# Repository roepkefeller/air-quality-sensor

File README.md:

# Air Quality Sensor

A DIY open-source air quality monitor built around an [ESP32-C3-WROOM-02](https://documentation.espressif.com/esp32-c3-wroom-02_datasheet_en.pdf), featuring a custom 4-layer PCB with four Sensirion/Bosch sensors, a laser-cut glass top panel, and a 3D-printed holder. Firmware runs on [ESPHome](https://esphome.io) and integrates natively with Home Assistant. An optional [PMSA003I particulate matter add-on](#particle-sensor-add-on) connects via the onboard QWIIC connector to add PM1.0, PM2.5, PM10, and EPA AQI measurements.

Installed boards are updated over the air: publishing a GitHub release makes a small [update server](#firmware-updates) on the home network build the firmware for every board, and Home Assistant offers it as a regular *Update available*. A [fault model](#sensor-fault-detection) watches every sensor not just for dropouts but also for frozen and drifting readings.

---

## Table of contents

- [What it measures](#what-it-measures)
- [System overview](#system-overview)
- [Hardware design](#hardware-design)
  - [Sensors](#sensors)
  - [Power system](#power-system)
  - [PCB](#pcb)
  - [Enclosure](#enclosure)
- [Assembly](#assembly)
  - [Soldering](#soldering)
  - [I2C addresses](#i2c-addresses)
  - [Power-on checklist](#power-on-checklist)
- [Firmware](#firmware)
  - [Getting started](#getting-started)
  - [Board configs](#board-configs)
  - [LED behavior](#led-behavior)
  - [Sensor fault detection](#sensor-fault-detection)
  - [Home Assistant entities](#home-assistant-entities)
  - [Web interface](#web-interface)
  - [Diagnostic configs](#diagnostic-configs)
- [Particle sensor add-on](#particle-sensor-add-on)
  - [Hardware](#hardware)
  - [Firmware (PM variant)](#firmware-pm-variant)
  - [Additional Home Assistant entities](#additional-home-assistant-entities)
- [Firmware updates](#firmware-updates)
  - [How it works](#how-it-works)
  - [Releasing a new version](#releasing-a-new-version)
  - [Update server](#update-server)
  - [CI](#ci)
- [Repository layout](#repository-layout)
- [Manufacturing](#manufacturing)
- [License](#license)

---

## What it measures

| Sensor | Measurements | Notes | Datasheet |
|--------|-------------|-------|-----------|
| **Sensirion SCD41** | CO₂ (ppm), temperature, humidity | Primary air quality signal | [PDF](https://sensirion.com/media/documents/48C4B7FB/67FE0194/CD_DS_SCD4x_Datasheet_D1.pdf) |
| **Sensirion SGP41** | VOC Index (1–500), NOx Index (1–500) | Always active; LED falls back to VOC if CO₂ unavailable | [PDF](https://sensirion.com/media/documents/5FE8673C/61E96F50/Sensirion_Gas_Sensors_Datasheet_SGP41.pdf) |
| **Sensirion SHT40** | Temperature (±0.2 °C), humidity (±1.8 %RH) | Reference for sensor compensation | [PDF](https://sensirion.com/resource/datasheet/sht4x) |
| **Bosch BMP280** | Barometric pressure, temperature | CO₂ altitude compensation source | [PDF](https://www.bosch-sensortec.com/media/boschsensortec/downloads/datasheets/bst-bmp280-ds001.pdf) |
| **Plantower PMSA003I** *(optional add-on)* | PM1.0, PM2.5, PM10 (µg/m³), particle counts | Via QWIIC connector; requires PM firmware variant | [PDF](docs/particle_sensor_addon/4505_PMSA003I_series_data_manual_English_V2.6.pdf) |

---

## System overview

The ESP32-C3 sits at the center of the design. All four sensors share a single I2C bus running at 50 kHz. The BMP280 pressure reading feeds the SCD41's ambient pressure compensation input. The firmware consolidates the three redundant temperature sensors and two humidity sensors into single median-based values, which in turn feed the SGP41's gas compensation algorithm. This cross-sensor compensation is why all four sensors are present even though some measurements overlap.

---

## Hardware design

### Sensors

**SCD41 — CO₂**

The SCD41 uses photoacoustic NDIR (non-dispersive infrared) technology to measure CO₂ directly. CO₂ is the primary metric for indoor air quality: levels above 1000 ppm are linked to reduced concentration, and above 2000 ppm cause noticeable cognitive effects. The SCD41 includes automatic self-calibration (ASC), which compensates for long-term sensor drift by assuming the sensor sees outdoor-quality air (≈400 ppm) for at least one hour per day. It also accepts an ambient pressure input from the BMP280 to correct for altitude-induced measurement error.

**SGP41 — VOC and NOx**

The SGP41 uses a metal oxide (MOX) sensing element to detect volatile organic compounds and nitrogen oxides. Rather than reporting raw concentrations, it outputs a processed index (1–500) where 100 represents a typical indoor baseline. This makes it well-suited for detecting events like cooking, cleaning products, paint fumes, or combustion without requiring gas-specific calibration. It also serves as the fallback air quality signal when CO₂ data is unavailable — the LED logic prefers CO₂ but degrades gracefully to VOC index.

**SHT40 — Temperature and humidity (reference)**

The SHT40 is the most accurate temperature and humidity sensor on the board, and it carries double weight in the firmware's median-based sensor fusion. The consolidated Temperature and Humidity entities shown in Home Assistant draw on all available sensors but are dominated by the SHT40 when it agrees with the others. The SCD41 and BMP280 also have internal temperature sensors, but they run warmer due to self-heating and contribute as secondary inputs.

All sensors on this board are affected by self-heating from the SGP41's MOX element (which runs an internal heater at ~400 °C), the ESP32-C3 Wi-Fi radio, and the power regulators. The firmware applies empirically calibrated offset corrections: −5.5 °C / +8 %RH for the SHT40, −5.5 °C for the BMP280, and −1.5 °C / +4 %RH for the SCD41. These values may need tuning — place a known-good reference thermometer next to the board, let everything stabilize for 30+ minutes, and adjust the offsets in the YAML until they match.

**BMP280 — Barometric pressure**

The BMP280 adds barometric pressure, which has two uses: it feeds the SCD41's ambient pressure compensation input (NDIR CO₂ sensors read differently at different altitudes), and it provides weather-correlation data for the Home Assistant dashboard.

**PMSA003I — Particulate matter (optional add-on)**

The Plantower PMSA003I is a laser scattering particle sensor that measures PM1.0, PM2.5, and PM10 mass concentrations as well as particle counts across six size bins (0.3–10 µm). It connects via the onboard QWIIC connector and is powered from the ESP32's 3.3 V buck rail. The firmware calculates a US EPA AQI from the PM2.5 reading and classifies the likely particle source from the PM2.5/PM10 ratio. See the [Particle sensor add-on](#particle-sensor-add-on) section for setup details.

---

### Power system

The board takes 5 V via USB-C. Any standard USB-C power supply rated ≥1 A works — no USB Power Delivery negotiation is required, and charge-only cables (no data lines) are fine.

The power path is:

**USB-C → TPD2EUSB30 (ESD protection) → PPTC fuse (750 mA self-resetting) → three separate 3.3 V rails**

Three regulators run in parallel off the 5 V bus, each feeding a dedicated load:

- **[TLV62569A](https://www.ti.com/lit/ds/symlink/tlv62569a.pdf)** (synchronous buck converter) → ESP32-C3 and QWIIC connector. The buck is efficient for the ESP32's variable current draw. The QWIIC connector shares this rail, keeping the sensitive sensor LDO rails free from expansion board loads.
- **[TLV755P](https://www.ti.com/lit/ds/symlink/tlv755p.pdf)** (LDO) → SCD41. The SCD41's photoacoustic CO₂ measurement is sensitive to supply noise; a dedicated LDO with a higher current rating than the TPS7A20 keeps its rail clean and isolated.
- **[TPS7A20](https://www.ti.com/lit/ds/symlink/tps7a20.pdf)** (ultra-low-noise LDO, 10 µVRMS) → SGP41, SHT40, and BMP280. The SGP41's MOX element and SHT40's capacitive humidity sensor are especially susceptible to supply noise; the TPS7A20 keeps all three on a single clean rail, isolated from both the buck and the SCD41's LDO.

The **PPTC fuse** is a self-resetting polyfuse rated at 750 mA, protecting the board against overcurrent faults without requiring manual intervention.

---

### PCB

<table>
  <tr>
    <td></td>
    <td></td>
  </tr>
  <tr>
    <td align="center"><em>Top copper layer</em></td>
    <td align="center"><em>Bottom copper layer</em></td>
  </tr>
</table>

<table>
  <tr>
    <td></td>
    <td></td>
  </tr>
  <tr>
    <td align="center"><em>Component side — ESP32, SCD41, regulators</em></td>
    <td align="center"><em>Bottom side — silkscreen</em></td>
  </tr>
</table>

The PCB is a 4-layer board designed in [KiCad](https://www.kicad.org/). Bare boards were manufactured by [JLCPCB](https://jlcpcb.com/) and assembled by hand.

Layer stackup: signal / GND plane / power plane / signal. The dedicated ground and power planes provide clean returns and reduce radiated noise — important given the sensitive gas sensors on the same board.

The board uses a mix of 0402 and 0603 passives, with all ICs in small SMD packages. The custom footprint for the SGP41 (`air_quality_footprints.pretty/`) is included in the repository because it is not in the standard KiCad library.

---

### Enclosure

*Sensor on a shelf in the bedroom (base variant, no PM add-on).*

The enclosure consists of three parts:

**3D-printed holder** (`hardware/enclosure/air_quality_sensor_holder.f3d`, `.stl`): holds the PCB and provides ventilation for the sensors. Print in PLA or PETG at 0.2 mm layer height. The PM variant uses a modified holder (`hardware/enclosure/particle_sensor_addon/air_quality_sensor_particle_sensor_addon_holder.f3d`, `.stl`) with a mount for the Adafruit PMSA003I breakout. It requires 2 additional M2 heat-set inserts (same type as used for the glass top) and 2 additional M2 screws (same as used for the glass top).

**Laser-cut glass top** (`hardware/enclosure/air_quality_sensor_glass_top.dxf`, `.step`, `.f3d`): 2 mm clear glass, sourced from [Formulor](https://www.formulor.de) using the provided DXF file.

**Standoffs**: [M2.5 × 10 mm male-female hex standoffs](https://www.amazon.de/dp/B0C1FY87PY) (5 mm across flats) mount between the PCB and the glass top. The Fusion 360 model is included at `hardware/enclosure/Standoff mf - M2.5 x 10 across flats 5mm.f3d`.

**Heated inserts**: [M2.5 heat-set inserts](https://www.amazon.de/dp/B0F2TGGBMC) are pressed into the 3D-printed holder with a soldering iron before screwing in the standoffs. This gives the plastic threads much better durability than screwing directly into printed material.

**Power supply and cable**: 5 V/1 A USB-A wall charger + USB-C to USB-A cable. Any charger rated ≥1 A works. Tested with: [RAVIAD USB-C Kabel 1 m (€3.99)](https://www.amazon.de/gp/product/B0GT379MW7) and [18W USB-A Ladegerät, 4er-Pack (€19.98)](https://www.amazon.de/gp/product/B0CRS1YX4S).

*Sensor installed in the living room (base variant, no PM add-on) — wall-mounted.*

---

## Assembly

### Soldering

All components are SMD. The board was assembled using solder paste and a hotplate for the initial reflow, followed by hand rework with a soldering iron for touch-ups.

Recommended soldering order — ICs and sensor packages before passives, connectors last:

1. **ESP32-C3-WROOM-02** — the largest IC; solder the pads around the perimeter, then reflow the exposed pad underneath with a hot-air station or by heating the board from below.
2. **TLV62569A, TLV755P, TPS7A20, TPD2EUSB30** — small SOT/WSON packages; drag-solder or use solder paste + hot air.
3. **SGP41** — custom footprint (`air_quality_footprints.pretty/`); ensure the exposed pad underneath is soldered for both mechanical and thermal contact.
4. **SCD41, SHT40, BMP280** — Sensirion LCC packages; reflow carefully, avoid excess heat on the SCD41 optical aperture.
5. **0402/0603 passives** — resistors and capacitors.
6. **USB-C connector, WS2812, LEDs, standoff holes** — connectors and through-board components last.

Use the interactive BOM (`hardware/pcb/air_quality_sensor/bom/ibom.html`) during assembly — it highlights each component on the board overlay and is the easiest way to avoid placing components in the wrong location. Open it locally in any browser, no server required.

The schematic PDF (`hardware/pcb/air_quality_sensor/air_quality_sensor-schematic.pdf`) is the reference for component values and net names.

### I2C addresses

| Sensor | I2C address | Configurable? |
|--------|-------------|---------------|
| SCD41 | 0x62 | No |
| SGP41 | 0x59 | No |
| SHT40 | 0x44 | No |
| BMP280 | 0x76 | Via SDIO pin (0x76 or 0x77) |
| PMSA003I *(PM add-on, optional)* | 0x12 | No |

The firmware enables I2C bus scanning on boot (`scan: true`). With a serial monitor connected, boot log output will list all detected addresses — a quick way to confirm all four sensors are soldered correctly and communicating before flashing the full config.

### Power-on checklist

Before flashing for the first time:

1. **Visual inspection** — check for solder bridges on the ESP32 and sensor pads under magnification.
2. **Continuity check** — verify no short between the three 3.3V rails, and no short between any rail and GND.
3. **Apply 5V via USB-C** — measure voltage on each 3.3V rail with a multimeter before the ESP32 is powered. Expected: ~3.3V on all three rails.
4. **Check quiescent current** — with sensors powered but ESP32 not yet flashed, current draw should be low (a few mA). A high reading suggests a solder bridge or incorrect component.
5. **Flash firmware** — once voltage rails check out, proceed to the firmware getting started section.
6. **Verify I2C scan** — open the serial monitor and confirm all four sensor addresses appear in the boot log.

---

## Firmware

The firmware is a single [ESPHome](https://esphome.io) YAML configuration. ESPHome compiles it to a native binary for the ESP32-C3 and handles OTA updates, the web server, and the Home Assistant native API automatically.

### Getting started

**Prerequisites:** ESPHome installed (`pip install esphome` or via the Home Assistant add-on).

1. Copy `firmware/secrets.yaml.example` to `firmware/secrets.yaml` and fill in all four values:

   ```yaml
   wifi_ssid: "your-network"
   wifi_password: "your-password"
   api_encryption_key: "your-base64-encryption-key"
   ota_password: "your-ota-password"
   ```

   The `api_encryption_key` is a 32-byte random key used to encrypt the connection between ESPHome and Home Assistant. Generate one with:

   ```bash
   openssl rand -base64 32
   ```

   Alternatively, run `esphome wizard firmware/air-quality-sensor.yaml` and ESPHome will generate and fill in all secrets interactively.

   The `ota_password` can be any string — you'll be prompted for it when pushing firmware updates over the air.

2. Flash via USB using the included wrapper script:

   ```bash
   cd firmware
   ./flash.sh Wohnzimmer                        # first flash: interactive port selection
   ./flash.sh Kueche --device 192.168.178.132   # target a known IP for OTA
   ```

   The `location` argument (e.g. `Wohnzimmer`, `Kueche`) is stamped into the device's friendly name in Home Assistant, so multiple boards are distinguishable. The script also derives the firmware version from git — the current tag if HEAD is tagged, otherwise `dev-YYYY-MM-DD`, with `-dirty` appended if there are uncommitted changes, and `-pm` appended for the PM variant (e.g. `v1.1.0-pm`, `v1.1.0-dirty-pm`). This makes the active variant immediately visible in Home Assistant.

   For manual invocation without the wrapper:

   ```bash
   esphome -s location "Wohnzimmer" -s firmware_version "dev-manual" run air-quality-sensor.yaml
   ```

3. Once a board is installed somewhere for good, give it a [board config](#board-configs) (`firmware/device-<room>.yaml`) and flash it once with `./flash.sh <room>`. From then on it receives [firmware updates](#firmware-updates) from GitHub releases and you install them from Home Assistant — no laptop needed.

**Multiple boards:** the firmware is designed to be shared across boards unchanged. `name_add_mac_suffix: true` appends the last 3 bytes of each board's WiFi MAC to its hostname (e.g. `air-quality-sensor-a1b2c3.local`), so boards don't conflict on the network. Only the location (and, for the kitchen, the PM variant) differs — pinned per board in its board config.

**Home Assistant:** once on the network the device is auto-discovered via the native API. Go to Settings → Integrations and accept the discovered device. All entities appear immediately.

---

### Board configs

Every installed board has a small config file in `firmware/` that fixes its installation location and firmware variant, so neither a release build nor a manual flash can mix them up:

| Board | MAC suffix | Config | Variant | Location (as flashed) |
|-------|-----------|--------|---------|-----------------------|
| Küche | b7f8c0 | `device-kueche.yaml` | base + [PM add-on](#particle-sensor-add-on) | `Kueche` |
| Schlafzimmer | b7f8b0 | `device-schlafzimmer.yaml` | base | `Schlafzimmer` |
| Wohnzimmer | b7f8b8 | `device-wohnzimmer.yaml` | base | `Wohnzimmer` |

Each file only sets `location`, `device_slug` (the board's folder on the update server) and its own build directory, then includes the base or PM firmware:

```yaml
substitutions:
  location: "Kueche"
  device_slug: "kueche"
esphome:
  build_path: build/aqs-kueche
packages:
  firmware: !include air-quality-sensor-pm.yaml
```

`location` becomes part of the device name in Home Assistant, so it must not change once a board is set up (the kitchen board is `Kueche` without umlaut because that's how it was first flashed; its display name was renamed in HA). Settings changed in HA — thresholds, LED brightness, counters — are stored on the board and survive every update.

Flash a board by its config name: `./flash.sh kueche` (optionally `--device <ip>`). **New board:** copy one of the files, set `location` and `device_slug`, flash it once — from then on it updates with the others.

---

### LED behavior

The WS2812 RGB LED on the board gives an at-a-glance air quality reading. The firmware prefers CO₂ from the SCD41 as the primary signal; if that sensor is unavailable, it falls back to the VOC index from the SGP41.

| Color | CO₂ (preferred) | VOC Index (fallback) |
|-------|-----------------|----------------------|
| 🟢 Green | < 800 ppm | < 150 |
| 🟡 Yellow | 800–1200 ppm | 150–250 |
| 🔴 Red | > 1200 ppm | > 250 |

All three thresholds (green→yellow, yellow→red, and a separate pulse threshold) are exposed as configurable Number entities in Home Assistant — no reflash needed to tune them. The defaults above apply on first boot.

Above the pulse threshold (default 1500 ppm CO₂ / 350 VOC), the LED switches from solid to a slow pulse (30–80% brightness, 1 s cycle) to draw attention to critically poor air quality.

Brightness defaults to 25% on first boot and is then fully user-controlled from Home Assistant. The chosen brightness persists across reboots. The LED can also be turned on/off from HA — the on/off state persists independently of brightness. Color updates are intentionally instant (no transition fade) so the reading snaps to the new value as soon as a sensor reports.

The LED driver is activated 5 seconds after boot to avoid a crash in the WS2812 driver before its internal buffer is initialized. During this window the LED stays off regardless of sensor data.

A second red LED (the fault LED) lights up whenever the [fault model](#sensor-fault-detection) considers any sensor faulty — dead, frozen or drifting. It re-evaluates every 30 seconds.

---

### Sensor fault detection

Checking only whether a sensor still publishes is not enough: in the field a BMP280 latched up and kept publishing the exact same temperature and pressure for 14 days while every liveness check stayed green. The fault model in `firmware/fault_detect.h` therefore treats a sensor as faulty if any of these hold:

| Rule | Condition |
|------|-----------|
| **Dead** | no value, or NaN |
| **Frozen** | every sample over a 15 min window is bit-identical — real sensors always have some ADC noise, so this needs no threshold |
| **Flat** | the value moves less than a per-signal span over 15 min *while another chip clearly moves* (so a quiet night doesn't trigger it) |
| **Drift** | a temperature sensor disagrees with the consensus of the others by more than 1.5 °C |

The detector samples every 30 s on its own schedule, so boost mode doesn't shorten the window. Stuck checks only start 20 minutes after boot. Self-calibrating signals that legitimately sit still (SGP41 VOC index, PM2.5 in clean air) are liveness-only; the PM add-on is watched through its 0.3 µm particle count instead, which always moves in real indoor air.

The result is shown as one **Sensor Fault** entity plus one fault entity per chip, a readable **Fault Detail** string (e.g. `SCD41 drift +2.4 °C`) and the fault LED. The **Span** diagnostic sensors show each signal's movement over the window — watch them for a few days before tightening a threshold.

For about 1–2 minutes after every reboot, sensors that haven't reported their first reading yet show up as offline or drifting and the fault LED lights; this clears by itself once all sensors are up.

**Testing the alarm path:** the *Debug Freeze BMP280* switch freezes the BMP280 values as seen by the detector (the sensor itself keeps publishing). After one window (15 min) the BMP280 fault, Fault Detail and fault LED fire end to end; switching it off clears them again. For faster tests flash with `-s fault_sample_interval 2s`. Host-side unit tests for the detector: `firmware/test/run_tests.sh`.

---

### Home Assistant entities

The device exposes a rich set of entities organized into three tiers in the HA device page:

**Primary (visible on the main card)**

| Entity | Description |
|--------|-------------|
| Temperature | Consolidated from SHT40, BMP280, SCD41 via median + outlier rejection (SHT40 weighted 2×) |
| Humidity | Consolidated from SHT40 and SCD41; SHT40 preferred if they disagree by > 10 %RH |
| CO₂ | Raw SCD41 reading with ambient pressure compensation from BMP280 |
| VOC Index | SGP41 MOX index (1–500, baseline 100), compensated with consolidated T/H |
| NOx Index | SGP41 NOx index (1–500) |
| Pressure | BMP280 barometric pressure |
| Absolute Humidity | Computed from consolidated T/H via Magnus–Tetens formula (g/m³) |
| Dew Point | Computed from consolidated T/H via Magnus formula (°C) |
| Air Quality Score | Weighted composite: CO₂ 40%, VOC 25%, NOx 15%, temperature comfort 10%, humidity comfort 10% (0–100%) |
| Comfort Zone | ASHRAE-inspired classification: Comfortable / Acceptable / Too cold / Too hot / Too dry / Too humid |
| Air Quality LED | RGB light entity — color and pulse controlled by firmware, brightness/on-off by user |
| Sensor Fault | Binary problem sensor — on if any sensor is dead, frozen or drifting (see [Sensor fault detection](#sensor-fault-detection)) |
| Firmware | Update entity — shows *Update available* when a newer release is on the [update server](#firmware-updates); install from HA |
| Particle Sensor Addon Found | Binary connectivity sensor — true if the PMSA003I responds on the I2C bus (probed on boot and every 30s). Present in both variants; also turns true in the base variant if the sensor is plugged in, indicating the PM firmware should be flashed. |

**Controls**

| Entity | Description |
|--------|-------------|
| Boost Mode | Switch — reduces all sensor update intervals from 30 s to 5 s for fast feedback (e.g. while cooking) |
| Threshold CO₂ Green→Yellow | Configurable ppm threshold (default 800) |
| Threshold CO₂ Yellow→Red | Configurable ppm threshold (default 1200) |
| Threshold CO₂ Pulse (Critical) | Triggers pulse effect above this level (default 1500 ppm) |
| Threshold VOC Green→Yellow | Configurable VOC index (default 150) |
| Threshold VOC Yellow→Red | Configurable VOC index (default 250) |
| Threshold VOC Pulse (Critical) | Triggers pulse effect above this level (default 350) |

**Diagnostics** (collapsed by default in HA)

Per-sensor raw values (Temperature SHT40/BMP280/SCD41, Humidity SHT40/SCD41), per-sensor health (0/100%), per-chip fault binary sensors (SHT40/BMP280/SCD41/SGP41 Fault), Fault Detail, Span sensors for stuck detection, peak CO₂/VOC/NOx/temperature/humidity since boot (taken from the consolidated values), time spent in each air quality category today (minutes), 5V rail voltage, uptime, reboot count, firmware version, temperature/humidity source attribution with drift annotation, last crash reason, last reset reason (power-on, software reset, watchdog, brownout …), and the *Debug Freeze BMP280* test switch.

Boost mode speeds up the derived entities (consolidated temperature/humidity, dew point, Air Quality Score) together with the raw sensors. The daily category counters are written to flash far less often than before (~15× fewer NVS writes).

---

### Web interface

The device runs a built-in web server on port 80. Because `name_add_mac_suffix` is enabled, the hostname includes the board's MAC suffix — navigate to `http://air-quality-sensor-XXXXXX.local` (the exact hostname is printed in the ESPHome boot log) or use the device's IP address directly. Any browser on the same network works.

*Base variant — the PM add-on entities are not shown.*

Diagnostic buttons available in the web UI and in Home Assistant:

| Button | Effect |
|--------|--------|
| **Test Fault LED** | Turns the fault LED on for 2 seconds — useful for confirming the LED is soldered and working. |
| **SCD41 Factory Reset** | Clears the SCD41's calibration history and restarts the ESP32. Use if CO₂ readings look wrong after long transport or storage. |
| **Reset Peak Values** | Resets all peak observations (CO₂, VOC, NOx, temperature, humidity) back to their initial sentinels, so the next reading establishes a new peak. |
| **Restart ESP** | Reboots the ESP32. |

If the device cannot reach your Wi-Fi network it falls back to an access point: SSID `Air-Quality Fallback`, password `configureme`. Connect to it and navigate to `http://192.168.4.1` to reconfigure.

---

### Diagnostic configs

Two additional ESPHome configs are included for debugging the SCD41:

| File | Purpose |
|------|---------|
| `diagnostic-scd41-only.yaml` | Runs only the SCD41 in isolation — useful for ruling out I2C address conflicts |
| `diagnostic-scd41-deep.yaml` | Extended SCD41 diagnostics with verbose sensor logging |

Flash a diagnostic config the same way as the main config:

```bash
esphome run firmware/diagnostic-scd41-only.yaml
```

---

## Particle sensor add-on

The QWIIC connector on the board exposes the I2C bus, allowing an [Adafruit PMSA003I Air Quality Breakout](https://www.adafruit.com/product/4632) to be connected without any soldering. This add-on extends the sensor with PM1.0, PM2.5, and PM10 mass concentration measurements, EPA AQI calculation, and particle source classification.

The PM variant is a separate firmware build that includes the base firmware plus an additional package. Both variants expose a **Particle Sensor Addon Found** binary sensor — it reflects whether the PMSA003I responds on the I2C bus, so even the base firmware turns it true if the sensor is plugged in, making it clear that the PM variant should be flashed.

### Hardware

Connect the Adafruit PMSA003I breakout to the board's QWIIC connector with a QWIIC cable — a 50 mm cable fits cleanly. No other wiring is needed; the breakout is powered and communicates entirely over the 4-pin QWIIC connector (3.3 V, GND, SDA, SCL). The PMSA003I appears at I2C address **0x12**.

The PMSA003I sensor module has mounting holes intended to screw it down to the breakout PCB, but Adafruit doesn't include screws — the module is only held by its connector pads, which isn't particularly solid. Double-sided tape between the module and the breakout PCB fixes this. The two remaining mounting holes on the breakout are used to screw the whole assembly to the holder.

**LED mod (recommended)**

The Adafruit PMSA003I breakout has a status LED that competes visually with the air quality LED on the main board — the air quality LED should be the primary indicator. The breakout's status LED resistor (R1) was changed from 10 kΩ to 100 kΩ to dim it significantly. Alternatively, the LED can be desoldered entirely.

*Sensor wall-mounted in the kitchen with PMSA003I PM add-on.*

### Firmware (PM variant)

Installed boards get the PM variant through their [board config](#board-configs) (`device-kueche.yaml` includes `air-quality-sensor-pm.yaml`), so `./flash.sh kueche` and release updates always build it with the add-on. For ad-hoc flashing, use the `--pm` flag:

```bash
cd firmware
./flash.sh Schlafzimmer --pm                           # first flash: interactive port selection
./flash.sh Schlafzimmer --pm --device 192.168.178.132  # OTA to a known IP
```

When switching between the base and PM variant, the flash script automatically cleans the build cache to avoid PlatformIO errors from stale component objects.

To revert to the base firmware without the PM package:

```bash
./flash.sh Schlafzimmer --device 192.168.178.132
```

### Additional Home Assistant entities

All entities below are added when flashing the PM variant. In the PM variant the PMSA003I is a required sensor: if it is missing from the I2C bus or stops reporting data, the fault LED lights up — same behaviour as the onboard sensors.

**Primary**

| Entity | Description |
|--------|-------------|
| PM 1.0 | Mass concentration of particles ≤ 1 µm (µg/m³) |
| PM 2.5 | Mass concentration of particles ≤ 2.5 µm (µg/m³) |
| PM 10.0 | Mass concentration of particles ≤ 10 µm (µg/m³) |
| EPA AQI (PM2.5) | US EPA Air Quality Index calculated from PM2.5 (0–500) |
| EPA AQI Category | Human-readable label: Good / Moderate / Unhealthy for Sensitive Groups / Unhealthy / Very Unhealthy / Hazardous |
| Air Quality Score (Extended) | Composite score (0–100%) with PM2.5 added at 15% weight; other weights rebalanced: CO₂ 35%, VOC 20%, NOx 15%, temperature/humidity comfort 7.5% each |
| Particle Source | Classification from PM2.5/PM10 ratio: Combustion (cooking / candles / traffic) / Mixed / Coarse (dust / pollen / abrasion) |

**Diagnostics**

| Entity | Description |
|--------|-------------|
| PMC >0.3 µm | Particle count per 0.1 L of air for particles > 0.3 µm |
| PMC >0.5 µm | Particle count per 0.1 L of air for particles > 0.5 µm |
| PMC >1.0 µm | Particle count per 0.1 L of air for particles > 1.0 µm |
| PMC >2.5 µm | Particle count per 0.1 L of air for particles > 2.5 µm |
| PMC >5.0 µm | Particle count per 0.1 L of air for particles > 5.0 µm |
| PMC >10.0 µm | Particle count per 0.1 L of air for particles > 10.0 µm |
| PMSA003I Fault / PMSA003I Health | The add-on as a regular chip in the fault model (liveness of PM2.5, frozen check on the 0.3 µm count) |
| PM Fault Minutes | How long the PM sensor has been faulted |
| PM Recovery Attempts | Reboots spent trying to recover it |

**Bus lockup recovery:** the PMSA003I occasionally holds the I2C data line low while still appearing on the bus. When the fault model flags it for 10 minutes, the board reboots, and the I2C bus recovery at boot clears the lockup. This is capped at 3 attempts (persisted across reboots), so a board whose add-on is really missing doesn't reboot forever; the budget resets as soon as the sensor reports again.

---

## Firmware updates

### How it works

```
GitHub release ──(checked every 10 min)──► update server (Proxmox LXC on the LAN)
                                            builds every firmware/device-*.yaml
                                            with the local secrets.yaml
                                            nginx: /<board>/manifest.json + .ota.bin
                                                       ▲
each board checks its own manifest every 6 h ──────────┘
        └──► Home Assistant: "Firmware" update entity → Settings → Updates → Install
```

- Each board has a **Firmware** update entity (ESPHome `update` platform `http_request`). It reads `http://aqs-firmware.fritz.box/<device_slug>/manifest.json`; if the version there differs from the installed one, Home Assistant shows *Update available* — titled "Luftqualitätssensor Firmware", with a link to the release — exactly like any other update.
- **Nothing installs on its own.** Click *Install* in HA; the board downloads the image, checks its MD5 and reboots into it.
- Because every board only reads its own manifest, the kitchen board can only ever receive the PM build, and no board can receive another room's name.
- Version strings match what `flash.sh` stamps: `v1.2.0` for base boards, `v1.2.0-pm` for the kitchen.
- Classic push OTA (`./flash.sh`, ESPHome dashboard, OTA password) keeps working for development and recovery.

### Releasing a new version

1. Merge to `main`.
2. Create a release on GitHub with a tag like `v1.2.0`. The release title becomes the update summary.
3. Within ~10 minutes the update server has built and published all boards (a few minutes per board). Home Assistant shows the update the next time the boards check (every 6 h) — or immediately via *Check for updates* / restarting a board.

**Pre-releases** are ignored by the server, so you can tag something without offering it. **Rollback:** on the server, `/usr/local/bin/aqs-release-watcher v1.1.0` republishes an older tag, which HA then offers as an update. The server keeps the last three images per board.

### Update server

Everything the server runs is versioned in [`tools/update-server/`](tools/update-server/) and identical to what's installed:

| File | Purpose |
|------|---------|
| `create-lxc.sh` | Creates the LXC on the Proxmox host (2 cores, 1.5 GB RAM + 1 GB swap, 16 GB disk, DHCP) |
| `setup.sh` | Installs nginx, git, a Python venv with the pinned ESPHome, the watcher and its timer; idempotent, re-run after changes |
| `aqs-release-watcher.sh` | Checks the latest GitHub release, checks out the tag, runs `tools/build-release.sh`, publishes |
| `aqs-release-watcher.service` / `.timer` | Runs the watcher every 10 minutes |
| `aqs-firmware.nginx.conf` | Serves `/srv/aqs-firmware` read-only to the boards |

The build itself is [`tools/build-release.sh`](tools/build-release.sh): it compiles every board config, and only publishes once all of them built — image first, manifest last — so the boards never see a half-finished release. The ESPHome version is pinned in `tools/requirements-build.txt`.

Current install: CT 106 `aqs-firmware` on the Proxmox host, Ubuntu 24.04, `192.168.178.151` / `aqs-firmware.fritz.box`. Rebuilding it from scratch:

```bash
# on the Proxmox host
bash tools/update-server/create-lxc.sh
# inside the new container
bash <(curl -fsSL https://raw.githubusercontent.com/roepkefeller/air-quality-sensor/main/tools/update-server/setup.sh)
# from the machine with firmware/secrets.yaml
scp firmware/secrets.yaml root@aqs-firmware.fritz.box:/etc/aqs-firmware/secrets.yaml
```

**Why it's built at home:** the firmware images contain the WiFi password, so they're never built or published on GitHub. The server also doesn't use a self-hosted GitHub runner — on a public repo a stranger's pull request could run code on it. It only *pulls* from GitHub; nothing on it is reachable from outside. `secrets.yaml` is the only piece deliberately not in the repo.

Details, troubleshooting and the bootstrap of new boards: [docs/ota-server.md](docs/ota-server.md).

### CI

[`.github/workflows/firmware-ci.yml`](.github/workflows/firmware-ci.yml) compiles all three board configs on every push with dummy secrets, runs the fault-detector unit tests, and checks that the OTA image ends up where the release build expects it. Nothing built there is published.

---

## Repository layout

| Path | Contents |
|------|----------|
| `firmware/air-quality-sensor.yaml` | Base firmware (all four onboard sensors) |
| `firmware/air-quality-sensor-pm.yaml`, `firmware/packages/pm-sensor.yaml` | PM variant (PMSA003I add-on) |
| `firmware/device-*.yaml` | [Board configs](#board-configs) — one per installed board |
| `firmware/fault_detect.h`, `firmware/reset_reason.h` | Fault model and reset-reason decoding |
| `firmware/test/` | Host-side unit tests for the fault model |
| `firmware/flash.sh` | Manual flashing (USB or push OTA) |
| `tools/build-release.sh`, `tools/requirements-build.txt` | Release build used by the update server |
| `tools/update-server/` | Complete [update server](#update-server) configuration |
| `.github/workflows/` | CI |
| `hardware/` | PCB (KiCad, Gerbers, BOM) and enclosure |
| `docs/` | Images, datasheets, [OTA/update-server guide](docs/ota-server.md) |

---

## Manufacturing

PCB production files are in `hardware/pcb/air_quality_sensor/jlcpcb/`:

| File | Purpose |
|------|---------|
| `gerber/GERBER-air_quality_sensor.zip` | Upload to JLCPCB (or any fab) to order the bare PCB |
| `production_files/BOM-air_quality_sensor.csv` | Bill of materials — use for sourcing components |
| `production_files/CPL-air_quality_sensor.csv` | Component placement file — reference for hand assembly positioning |

Order the bare PCB from JLCPCB using the Gerber zip. Source components separately (Mouser, LCSC, DigiKey) using the BOM, then assemble by hand — see the [Assembly](#assembly) section above for the recommended process.

The schematic PDF (`hardware/pcb/air_quality_sensor/air_quality_sensor-schematic.pdf`) and interactive BOM (`hardware/pcb/air_quality_sensor/bom/ibom.html`) are the primary references during assembly.

---

## License

Hardware (PCB schematics, layout, enclosure files) is licensed under the [CERN Open Hardware Licence Version 2 – Strongly Reciprocal (CERN-OHL-S-2.0)](https://ohwr.org/cern_ohl_s_v2.txt).

Firmware is licensed under the [MIT License](https://opensource.org/licenses/MIT).

In short: you can use, modify, and manufacture this design freely — including commercially — as long as any modifications to the hardware are released under the same licence.

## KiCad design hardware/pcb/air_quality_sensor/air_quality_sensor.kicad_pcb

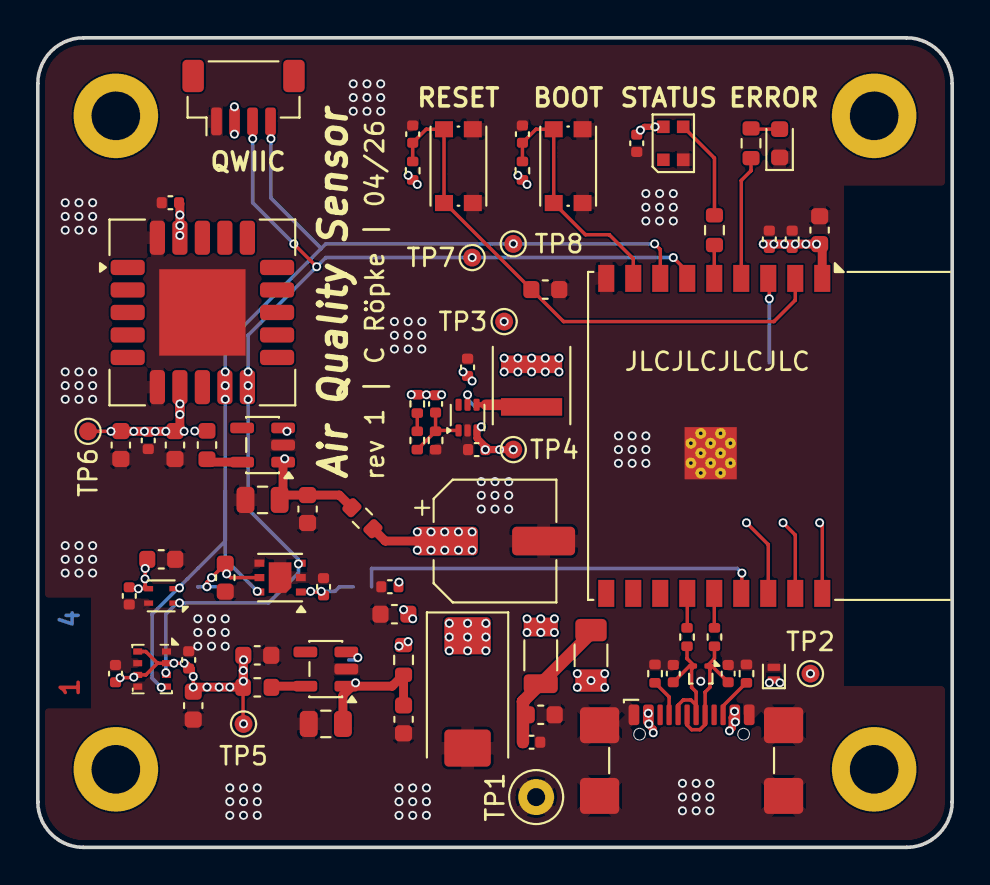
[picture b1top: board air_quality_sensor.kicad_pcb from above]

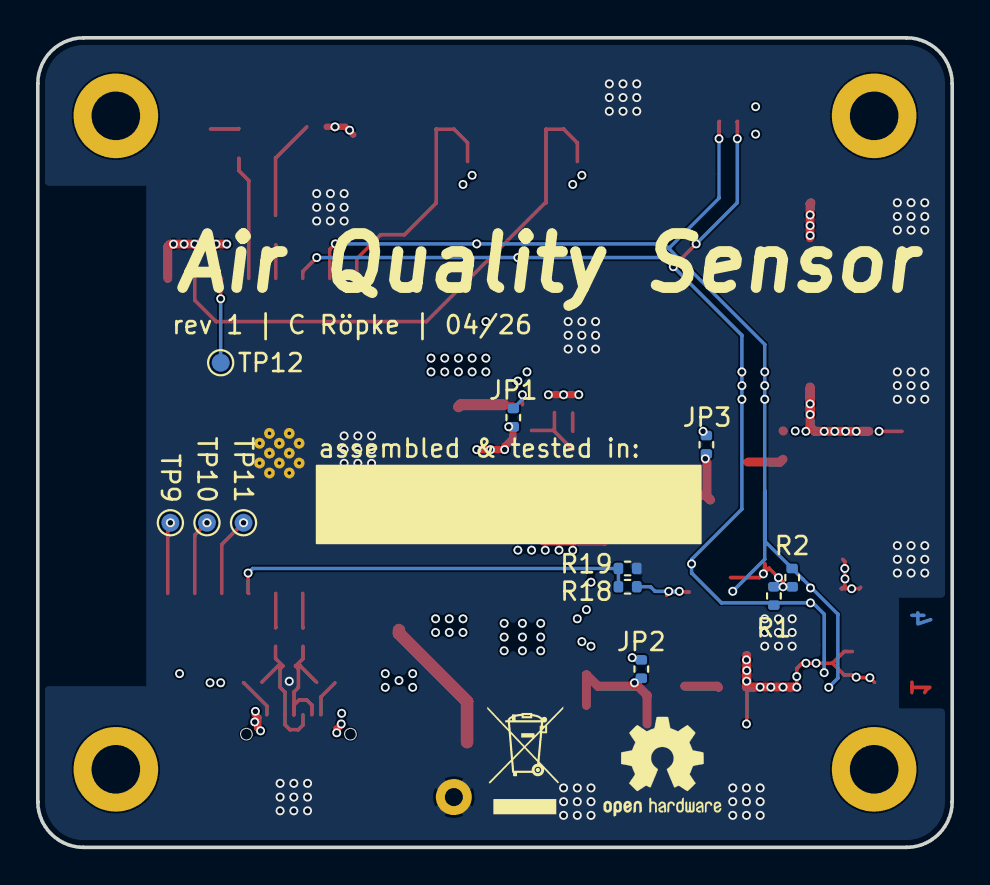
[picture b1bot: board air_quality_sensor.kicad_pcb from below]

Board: 4 copper layers, 50.8 x 45.0 mm, 91 parts (11 on the bottom side), 36 nets.

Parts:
C1: 4.7µ/10V/X5R; C_0402_1005Metric
C2, C3, C5, C12, C13, C21, C22, C25, C30, C31, C34: 100n/10V/X5R; C_0402_1005Metric
C4, C9, C10: 10p/10V/C0G; C_0402_1005Metric
C6, C29: 22µ/10V/X5R; C_0402_1005Metric
C7, C8, C11, C17, C18, C19, C20, C24, C26, C28, C32, C33: 1µ/10V/X5R; C_0603_1608Metric
C14, C27: 47µ/10V/X5R; C_0805_2012Metric
C15: 100µ/16V; CP_EIA-7343-20_Kemet-V
C16: 1µ/10V/X5R; C_0402_1005Metric
C23: 47u/16V/20%; CP_Elec_6.3x7.7
D1: ESDALC5; D_SOD-882
D2: LED 0603 red; LED_0603_1608Metric
D3: WS2812; LED_WS2812B-2020_PLCC4_2.0x2.0mm
F1: PPTC 8V 750mA; Fuse_1206_3216Metric
FB1, FB3: 1k@100MHz; L_0603_1608Metric
FB2: 1k@100MHz; L_1206_3216Metric
H1, H2, H3, H4: M3_MountingHole; MountingHole_2.7mm_M2.5_DIN965_Pad
J1: USB4110; USB_C_Receptacle_GCT_USB4110
J2: QWIIC Connector; JST_SH_BM04B-SRSS-TB_1x04-1MP_P1.00mm_Vertical
JP1, JP2, JP3: 0/1%; R_0402_1005Metric
L1: 1uH/20%/9.6A; L_Coilcraft_XxL4020
R1, R2: 4.7k/1%; R_0402_1005Metric
R3, R9: 22/1%; R_0402_1005Metric
R4, R5: 5.1k/1%; R_0402_1005Metric
R6: 270k/1%; R_0402_1005Metric
R7: 180k/1%; R_0402_1005Metric
R8: 100k/1%; R_0402_1005Metric
R10, R12: 330/1%; R_0603_1608Metric
R11: 36/1%; R_0603_1608Metric
R13: 0/1%; R_0603_1608Metric
R14, R15, R18, R19: 10k/1%; R_0402_1005Metric
SW1, SW2: Push_Button; SW_Push_1P1T_NO_CK_KMR2
TP1: GND; TestPoint_Loop_D2.50mm_Drill1.0mm
TP2: VBUS; TestPoint_Pad_D1.0mm
TP3: +3V3; TestPoint_Pad_D1.0mm
TP4: 5V; TestPoint_Pad_D1.0mm
TP5: +3V3_SENS; TestPoint_Pad_D1.0mm
TP6: 3V3_SCD; TestPoint_Pad_D1.0mm
TP7: SDA; TestPoint_Pad_D1.0mm
TP8: SCL; TestPoint_Pad_D1.0mm
TP9: IO0; TestPoint_Pad_D1.0mm
TP10: IO1; TestPoint_Pad_D1.0mm
TP11: IO2; TestPoint_Pad_D1.0mm
TP12: ADC1_CH4; TestPoint_Pad_D1.0mm
U1: TLV62569A; SOT-563
U2: SHT40; Sensirion_DFN-4_1.5x1.5mm_P0.8mm_SHT4x_NoCentralPad
U3: BMP280; Bosch_LGA-8_2x2.5mm_P0.65mm_ClockwisePinNumbering
U4: TPD2EUSB30; Texas_DRT-3
U5: SCD41; Sensirion_SCD4x-1EP_10.1x10.1mm_P1.25mm_EP4.8x4.8mm
U6: SGP41; XDCR_SGP41-D-R4
U7: TPS7A20; SOT-23-5
U8: ESP32-C3-WROOM-02
U9: TLV75533P; SOT-23-5

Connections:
+3V3: C6.1, C10.1, C29.1, C31.1, C33.1, J2.2, L1.2, R6.1, R14.1, R15.1, TP3.1 (1_1), U8.1 (3V3)
+3V3_SCD: C13.1, C18.1, C32.1, C34.1, FB1.2, TP6.1 (1_1), U5.7 (VDD), U5.19 (VDD)
+3V3_SENS: C2.1, C3.1, C5.1, C7.1, C8.1, C16.1, C20.1, C24.1, FB3.2, R1.1, R2.1, R18.1, TP5.1 (1_1), U2.3 (VDD), U3.2 (CSB), U3.6 (VDDIO), U3.8 (VDD), U6.1 (VDD), U6.5 (VDDH)
+5V: C1.1, C15.1, C19.1, C21.1, C22.1, C23.1, D3.4 (VDD), FB2.2, JP1.1 (A), R11.1, R13.1, TP4.1 (1_1), U1.3 (VIN)
/ESP32_ADC1_CH3: R18.2, R19.1, U8.15 (IO3)
/ESP32_ADC1_CH4: TP12.1 (1_1), U8.3 (IO4)
/ESP32_BOOT_SEL: C30.1, R15.2, SW2.2, U8.8 (IO9)
/ESP32_EN: C25.1, C26.1, R14.2, SW1.2, U8.2 (EN)
/ESP32_EN_LED: R10.1, U8.4 (IO5)
/ESP32_NEOP_DIN: R12.1, U8.5 (IO6)
/ESP32_SCL: J2.4, R2.2, TP8.1 (1_1), U2.2 (SCL), U3.4 (SCK), U5.9 (SCL), U6.6 (SCL), U8.7 (IO8)
/ESP32_SDA: J2.3, R1.2, TP7.1 (1_1), U2.1 (SDA), U3.3 (SDI), U5.10 (SDA), U6.3 (SDA), U8.6 (IO7)
/ESP32_USB_D+: R3.2, U8.14 (IO19)
/ESP32_USB_D-: R9.2, U8.13 (IO18)
/USB_D+: C4.1, J1.A6 (D+), J1.B6 (D+), R3.1, U4.1 (D+)
/USB_D-: C9.1, J1.A7 (D-), J1.B7 (D-), R9.1, U4.2 (D-)
GND: C1.2, C2.2, C3.2, C4.2, C5.2, C6.2, C7.2, C8.2, C9.2, C11.2, C12.2, C13.2, C14.2, C15.2, C16.2, C17.2, C18.2, C19.2, C20.2, C21.2, C22.2, C23.2, C24.2, C25.2, C26.2, C27.2, C28.2, C29.2, C30.2, C31.2, C32.2, C33.2, C34.2, D1.2 (A), D2.1 (K), D3.2 (VSS), J1.A1 (GND), J1.A12 (GND), J1.B1 (GND), J1.B12 (GND), J1.S1 (SHIELD), J2.1, R4.2, R5.2, R8.2, R19.2, SW1.1, SW2.1, TP1.1 (1_1), U1.2 (GND), U2.4 (VSS), U3.1 (GND), U3.5 (SDO), U3.7 (GND), U4.3 (GND), U5.6 (GND), U5.20 (GND), U5.21 (GND), U6.2 (VSS), U6.4 (N/A), U6.7 (EP), U7.2 (GND), U8.9 (GND), U8.19 (GND), U9.2 (GND)
unnamed: C11.1, C12.1, F1.2, FB2.1
unnamed: D2.2 (A), R10.2
unnamed: D3.3 (DIN), R12.2
unnamed: J1.A5 (CC1), R4.1
unnamed: J1.B5 (CC2), R5.1
unnamed: JP1.2 (B), U1.5 (EN)
unnamed: C14.1, C17.1, JP2.1 (A), R11.2, U7.1 (IN)
unnamed: JP2.2 (B), U7.3 (EN)
unnamed: C27.1, C28.1, JP3.1 (A), R13.2, U9.1 (IN)
unnamed: JP3.2 (B), U9.3 (EN)
unnamed: R6.2, R7.1
unnamed: C10.2, R7.2, R8.1, U1.1 (FB)
unnamed: L1.1, U1.4 (SW)
unnamed: FB3.1, U7.5 (OUT)
unnamed: TP9.1 (1_1), U8.18 (IO0)
unnamed: TP10.1 (1_1), U8.17 (IO1)
unnamed: TP11.1 (1_1), U8.16 (IO2)
unnamed: FB1.1, U9.5 (OUT)
VBUS: D1.1 (K), F1.1, J1.A4 (VBUS), J1.A9 (VBUS), J1.B4 (VBUS), J1.B9 (VBUS), TP2.1 (1_1)

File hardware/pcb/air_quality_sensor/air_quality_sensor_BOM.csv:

"Reference","Qty","DNP","Footprint","Manufacturer (MFR)","Value","Manufacturer Part Number (MPN)","Datasheet","Comments"
"C1","1","","Capacitor_SMD:C_0402_1005Metric","KYOCERA AVX","4.7µ/10V/X5R","0402ZD475KAT2A","",""
"C2,C3,C5,C12,C13,C21,C22,C25,C30,C31,C34","11","","Capacitor_SMD:C_0402_1005Metric","YAGEO","100n/10V/X5R","CC0402KPX5R6BB104","",""
"C4,C9","2","","Capacitor_SMD:C_0402_1005Metric","KEMET","10p/10V/C0G","C0402C100J8GACTU","",""
"C6,C29","2","","Capacitor_SMD:C_0402_1005Metric","Murata","22µ/10V/X5R","GRM158R61A226ME15D","",""
"C7,C8,C11,C17,C18,C19,C20,C24,C26,C28,C32,C33","12","","Capacitor_SMD:C_0603_1608Metric","YAGEO","1µ/10V/X5R","CC0603KRX5R6BB105","",""
"C10","1","DNP","Capacitor_SMD:C_0402_1005Metric","KEMET","10p/10V/C0G","C0402C100J8GACTU","",""
"C14,C27","2","","Capacitor_SMD:C_0805_2012Metric","Murata","47µ/10V/X5R","GRM21BR61A476ME15L","",""
"C15","1","","Capacitor_Tantalum_SMD:CP_EIA-7343-20_Kemet-V","Kyocera AVX","100µ/16V","TCJY107M016R0050","",""
"C16","1","","Capacitor_SMD:C_0402_1005Metric","YAGEO","1µ/10V/X5R","CC0402KPX5R6BB104","",""
"C23","1","","Capacitor_SMD:CP_Elec_6.3x7.7","Panasonic","47u/16V/20%","EEE-HC1E470XP","",""
"D1","1","","Diode_SMD:D_SOD-882","ST Microelectronics","ESDALC5","ESDALC5-1BM2","kicad-embed://esdalc5-1bm2.pdf",""
"D2","1","","LED_SMD:LED_0603_1608Metric","LITEON","LED 0603 red","LTST-C190EKT","https://www.mouser.com/catalog/specsheets/lite-on_lites05751-1.pdf",""
"D3","1","","LED_SMD:LED_WS2812B-2020_PLCC4_2.0x2.0mm","Worldsemi","WS2812","WS2812B-2020","https://cdn-shop.adafruit.com/product-files/4684/4684_WS2812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",""
"F1","1","","Fuse:Fuse_1206_3216Metric","Littelfuse","PPTC 8V 750mA","1206L075THYR","https://www.littelfuse.com/assetdocs/resettable-ptcs-1206l-d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",""
"FB1,FB3","2","","Inductor_SMD:L_0603_1608Metric","Murata Electronics","1k@100MHz","BLM18KG102SN1D","https://www.lcsc.com/datasheet/C160982.pdf",""
"FB2","1","","Inductor_SMD:L_1206_3216Metric","Murata Electronics","1k@100MHz","BLM31KN102SH1L","https://www.mouser.de/datasheet/3/76/1/QNFA9148.pdf",""
"J1","1","","Connector_USB:USB_C_Receptacle_GCT_USB4110","GCT","USB4110","USB4110-GF-A ","https://www.usb.org/sites/default/files/documents/usb_type-c.zip",""
"J2","1","","Connector_JST:JST_SH_BM04B-SRSS-TB_1x04-1MP_P1.00mm_Vertical","JST","QWIIC Connector","BM04B-SRSS-TB(LF)(SN)","",""
"JP1,JP2,JP3","3","","Resistor_SMD:R_0402_1005Metric","","0/1%","","",""
"L1","1","","Inductor_SMD:L_Coilcraft_XxL4020","Coilcraft","1uH/20%/9.6A","XEL4020-102MEC","https://4donline.ihs.com/images/VipMasterIC/IC/COLC/COLC-S-A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",""
"R1,R2","2","","Resistor_SMD:R_0402_1005Metric","","4.7k/1%","","",""
"R3,R9","2","","Resistor_SMD:R_0402_1005Metric","","22/1%","","",""
"R4,R5","2","","Resistor_SMD:R_0402_1005Metric","","5.1k/1%","","",""
"R6","1","","Resistor_SMD:R_0402_1005Metric","","270k/1%","","",""
"R7","1","","Resistor_SMD:R_0402_1005Metric","","180k/1%","","",""
"R8","1","","Resistor_SMD:R_0402_1005Metric","","100k/1%","","",""
"R10,R12","2","","Resistor_SMD:R_0603_1608Metric","","330/1%","","",""
"R11","1","","Resistor_SMD:R_0603_1608Metric","","36/1%","","",""
"R13","1","","Resistor_SMD:R_0603_1608Metric","","0/1%","","",""
"R14,R15,R18,R19","4","","Resistor_SMD:R_0402_1005Metric","","10k/1%","","",""
"SW1,SW2","2","","Button_Switch_SMD:SW_Push_1P1T_NO_CK_KMR2","C&K","Push_Button","KMR621NG_LFS","https://www.ckswitches.com/media/1907/kmr6.pdf",""
"U1","1","","Package_TO_SOT_SMD:SOT-563","Texas Instruments","TLV62569A","TLV62569ADRLT","https://www.ti.com/lit/gpn/tlv62569a",""
"U2","1","","Sensor_Humidity:Sensirion_DFN-4_1.5x1.5mm_P0.8mm_SHT4x_NoCentralPad","Sensirion","SHT40","SHT40-AD1B-R2","https://www.mouser.de/datasheet/3/1278/1/HT_DS_Datasheet_SHT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",""
"U3","1","","Package_LGA:Bosch_LGA-8_2x2.5mm_P0.65mm_ClockwisePinNumbering","Bosch Sensortec","BMP280","BMP280","https://cdn-shop.adafruit.com/datasheets/BST-BMP280-DS001-11.pdf",""
"U4","1","","Package_TO_SOT_SMD:Texas_DRT-3","Texas Instruments","TPD2EUSB30","TPD2EUSB30DRTR","http://www.ti.com/lit/ds/symlink/tpd2eusb30a.pdf",""
"U5","1","","Sensor:Sensirion_SCD4x-1EP_10.1x10.1mm_P1.25mm_EP4.8x4.8mm","Sensirion","SCD41","SCD41-D-R2","https://sensirion.com/media/documents/E0F04247/631EF271/CD_D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","very temperature sensitive! Use low-temp solder paste!"
"U6","1","","air_quality_footprints:XDCR_SGP41-D-R4","Sensirion","SGP41","SGP41-D-R4","https://sensirion.com/media/documents/5FE8673C/61E96F50/Sens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",""
"U7","1","","Package_TO_SOT_SMD:SOT-23-5","Texas Instruments","TPS7A20","TPS7A2033PDBVR","https://www.ti.com/lit/ds/symlink/tps7a20.pdf",""
"U8","1","","RF_Module:ESP32-C3-WROOM-02","Espressif","ESP32-C3-WROOM-02","ESP32-C3-WROOM-02","https://www.espressif.com/sites/default/files/documentation/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",""
"U9","1","","Package_TO_SOT_SMD:SOT-23-5","Texas Instruments","TLV75533P"," TLV75533PDBVR","https://www.ti.com/lit/ds/symlink/tlv755p.pdf","Alternative: Diodes Inc. AP2112K-3.3TRG1 "

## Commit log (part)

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2026-04-17 initial commit - rev1 ordered at jlcpcb 04/26
2026-06-10 changed folder structure
2026-06-11 reworked folder structure and created first README
2026-06-14 Fix LED boot crash, persist brightness, add self-heating offsets
    - Guard LED script with 5s boot delay to avoid WS2812 driver crash
    - Persist user brightness in dedicated NVS global instead of remote_values
    - Drop LED transition fade (instant color updates)
    - Add empirical self-heating offsets: SHT40 −5.5 °C/+8 %RH,
    SCD41 −1.5 °C/+4 %RH, BMP280 −5.5 °C
2026-06-23 changed C16 to 1uF to prevent SGP41 from making weird noises..
